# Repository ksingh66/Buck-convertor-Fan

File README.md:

# Outline
 We power a fan motor with a PWM controlled MOSFET that takes power from our buck convertor. We build both the 555 timer based PWM signal as well as the buck convertor. **View the BOM for parts to buy**.
 The DPDT switch we use to power this fan allows us to control which direction the fan rotates in also.

## Design for 555 timer PWM
 Important to note that instead of the LED we will supply power to a MOSFET 
 
### Soldered version 
Adjusting the blue dial adjusts the LED's brightness.

## Design for Buck convertor 
Due to my EAGLE subscription running out, I can only show this design by pictures of the board. However the schematic design is still uploaded to be used.

### Soldered final version
Watch the video here https://youtube.com/shorts/8-QiAdpP1wY
# Thank you for your time

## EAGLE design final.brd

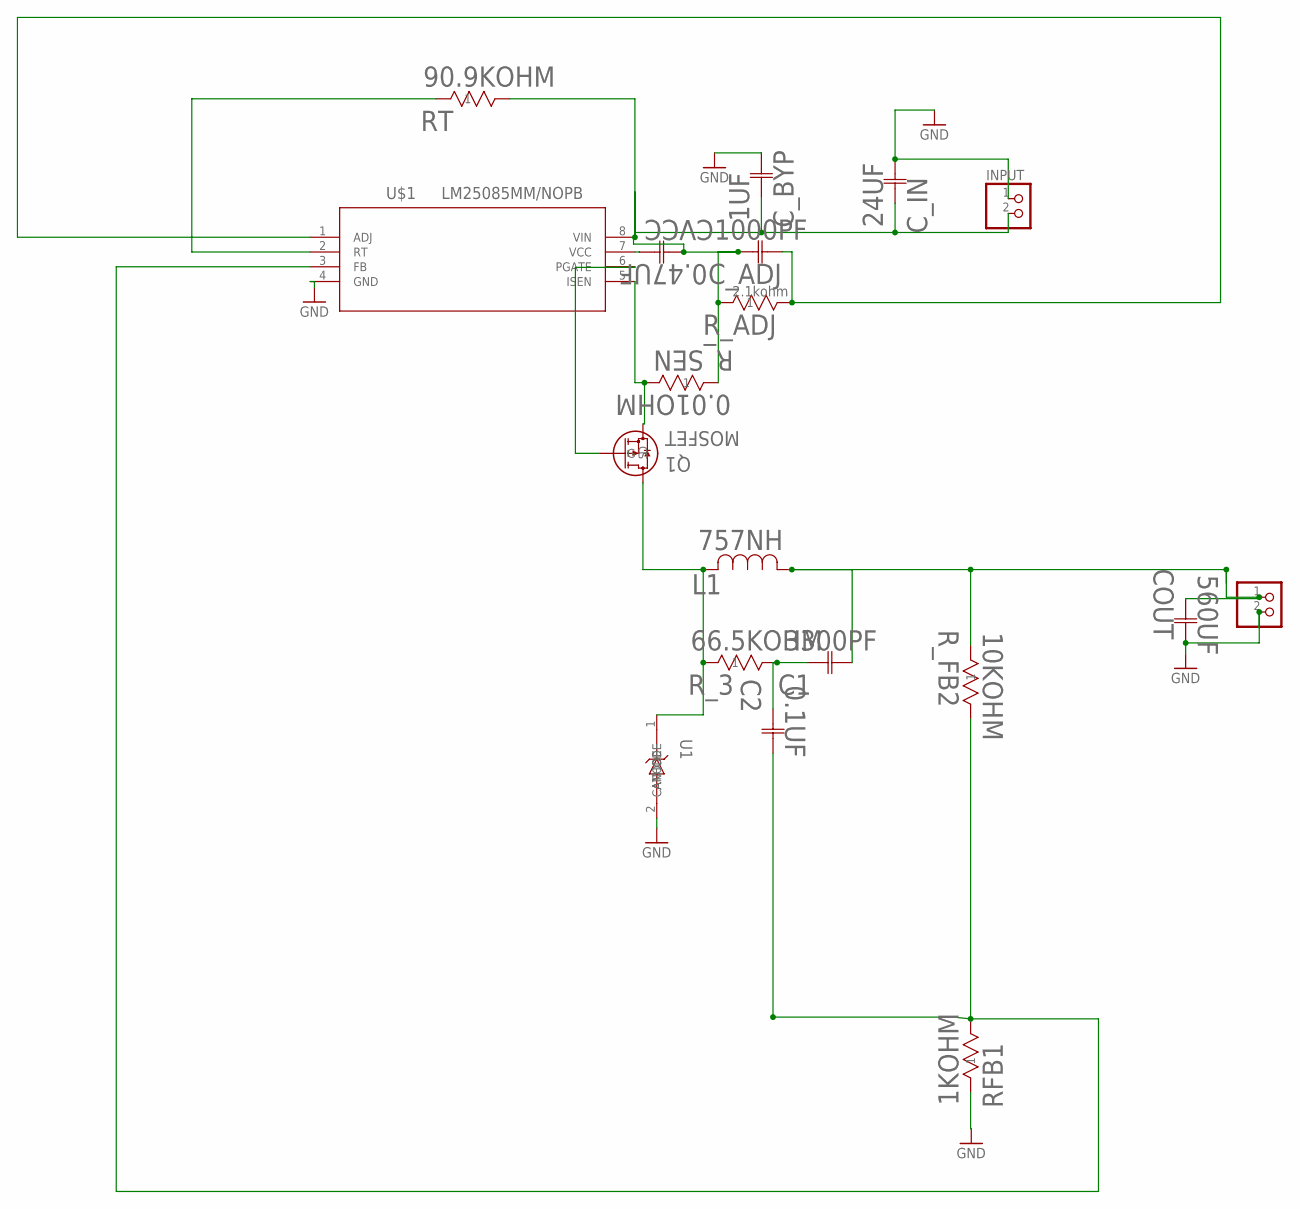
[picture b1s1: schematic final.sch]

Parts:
0.01OHM: R_SEN; STA_MPR5_STP
0.1UF: C2; U2-D_NCH
0.47UF: CVCC; CAP_WCAP-ATG8_05.0X11.0_WRE
1KOHM: RFB1; STA_CF14_STP
1UF: C_BYP; CAP_FG26_TDK
2.1KOHM: R_ADJ; STA_RNF14_STP
10KOHM: R_FB2; STA_CF14_STP
24UF: C_IN; CAP_5X11_WRE
66.5KOHM: R_3; RES_CMF50_VIS
90.9KOHM: RT; YAG_MF25_YAG
560UF: COUT; CAP_PAN_10X20_PAN
757NH: L1; IND_TAIYO_NRS6020_TAY
1000PF: C_ADJ; CAP_VY1_Y5U_9X5X13-10_VIS
3300PF: C1; G-21_MUR
INPUT: PINHD-1X2; 1X02
OUTPUT: PINHD-1X2; 1X02
Q1: MOSFET; SOT-23_DMP2123L_DIO
U1: DIODE; CASE_267-05_ONS
U$1: LM25085MM/NOPB; MUA08A

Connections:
GND: 1KOHM.1, 1UF.2, 24UF.2, 560UF.2, INPUT.1, OUTPUT.2, U1.2 (ANODE), U$1.4 (GND)
unnamed: Q1.1 (G), U$1.6 (PGATE)
unnamed: 0.1UF.2, 1KOHM.2, 10KOHM.2, U$1.3 (FB)
unnamed: 0.47UF.2, U$1.7 (VCC)
unnamed: 90.9KOHM.1, U$1.2 (RT)
unnamed: 2.1KOHM.2, 1000PF.2, U$1.1 (ADJ)
unnamed: 0.01OHM.2, Q1.3 (S), U$1.5 (ISEN)
unnamed: 0.01OHM.1, 0.47UF.1, 1UF.1, 2.1KOHM.1, 24UF.1, 90.9KOHM.2, 1000PF.1, INPUT.2, U$1.8 (VIN)
unnamed: 66.5KOHM.1, 757NH.2, Q1.2 (D), U1.1 (CATHODE)
unnamed: 0.1UF.1, 66.5KOHM.2, 3300PF.1
unnamed: 10KOHM.1, 560UF.1, 757NH.1, 3300PF.2, OUTPUT.1

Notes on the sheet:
2.1kohm

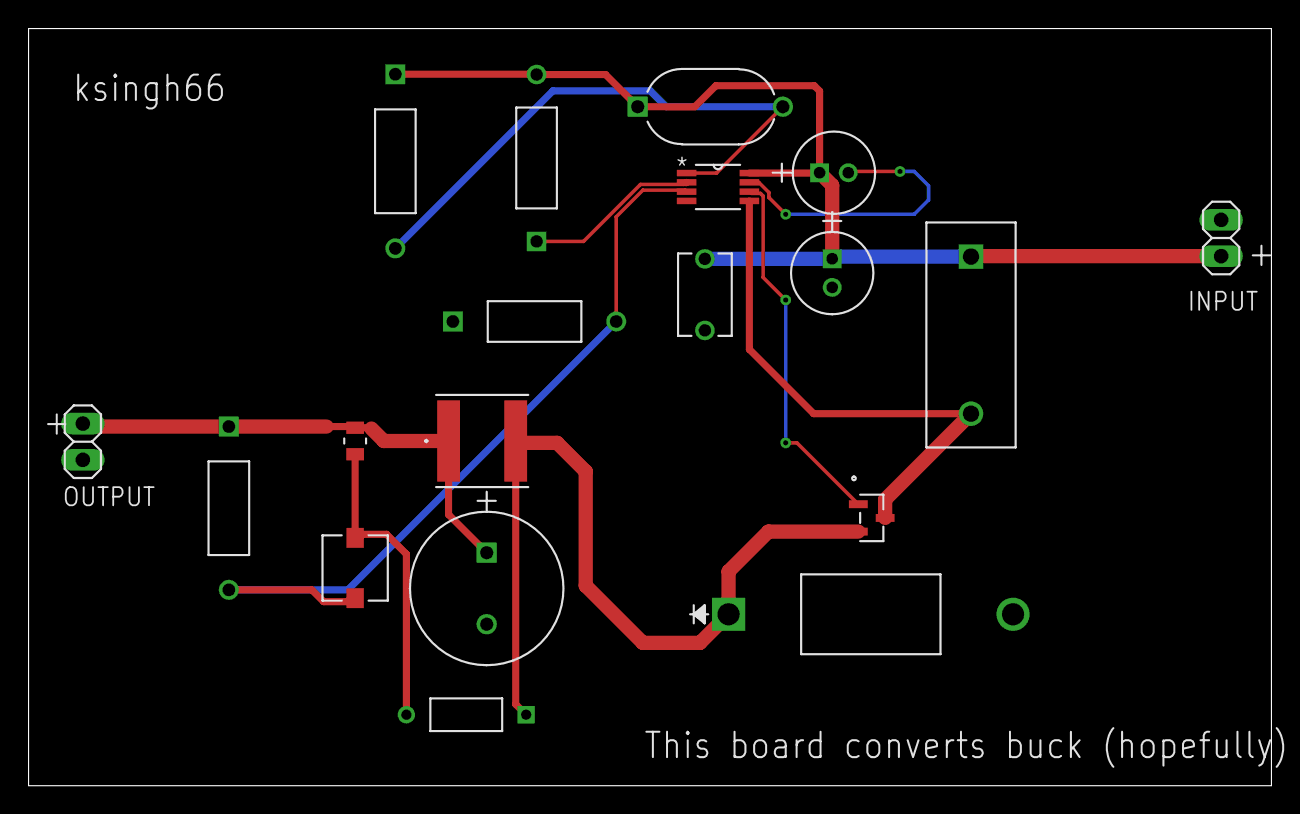
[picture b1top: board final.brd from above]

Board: 2 copper layers, 87.0 x 53.0 mm, 19 parts (0 on the bottom side), 11 nets.

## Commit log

2024-07-12 initial push

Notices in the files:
parts and their libraries:
COPYRIGHT: Copyright (C) 2023 Ultra Librarian. All rights reserved.
